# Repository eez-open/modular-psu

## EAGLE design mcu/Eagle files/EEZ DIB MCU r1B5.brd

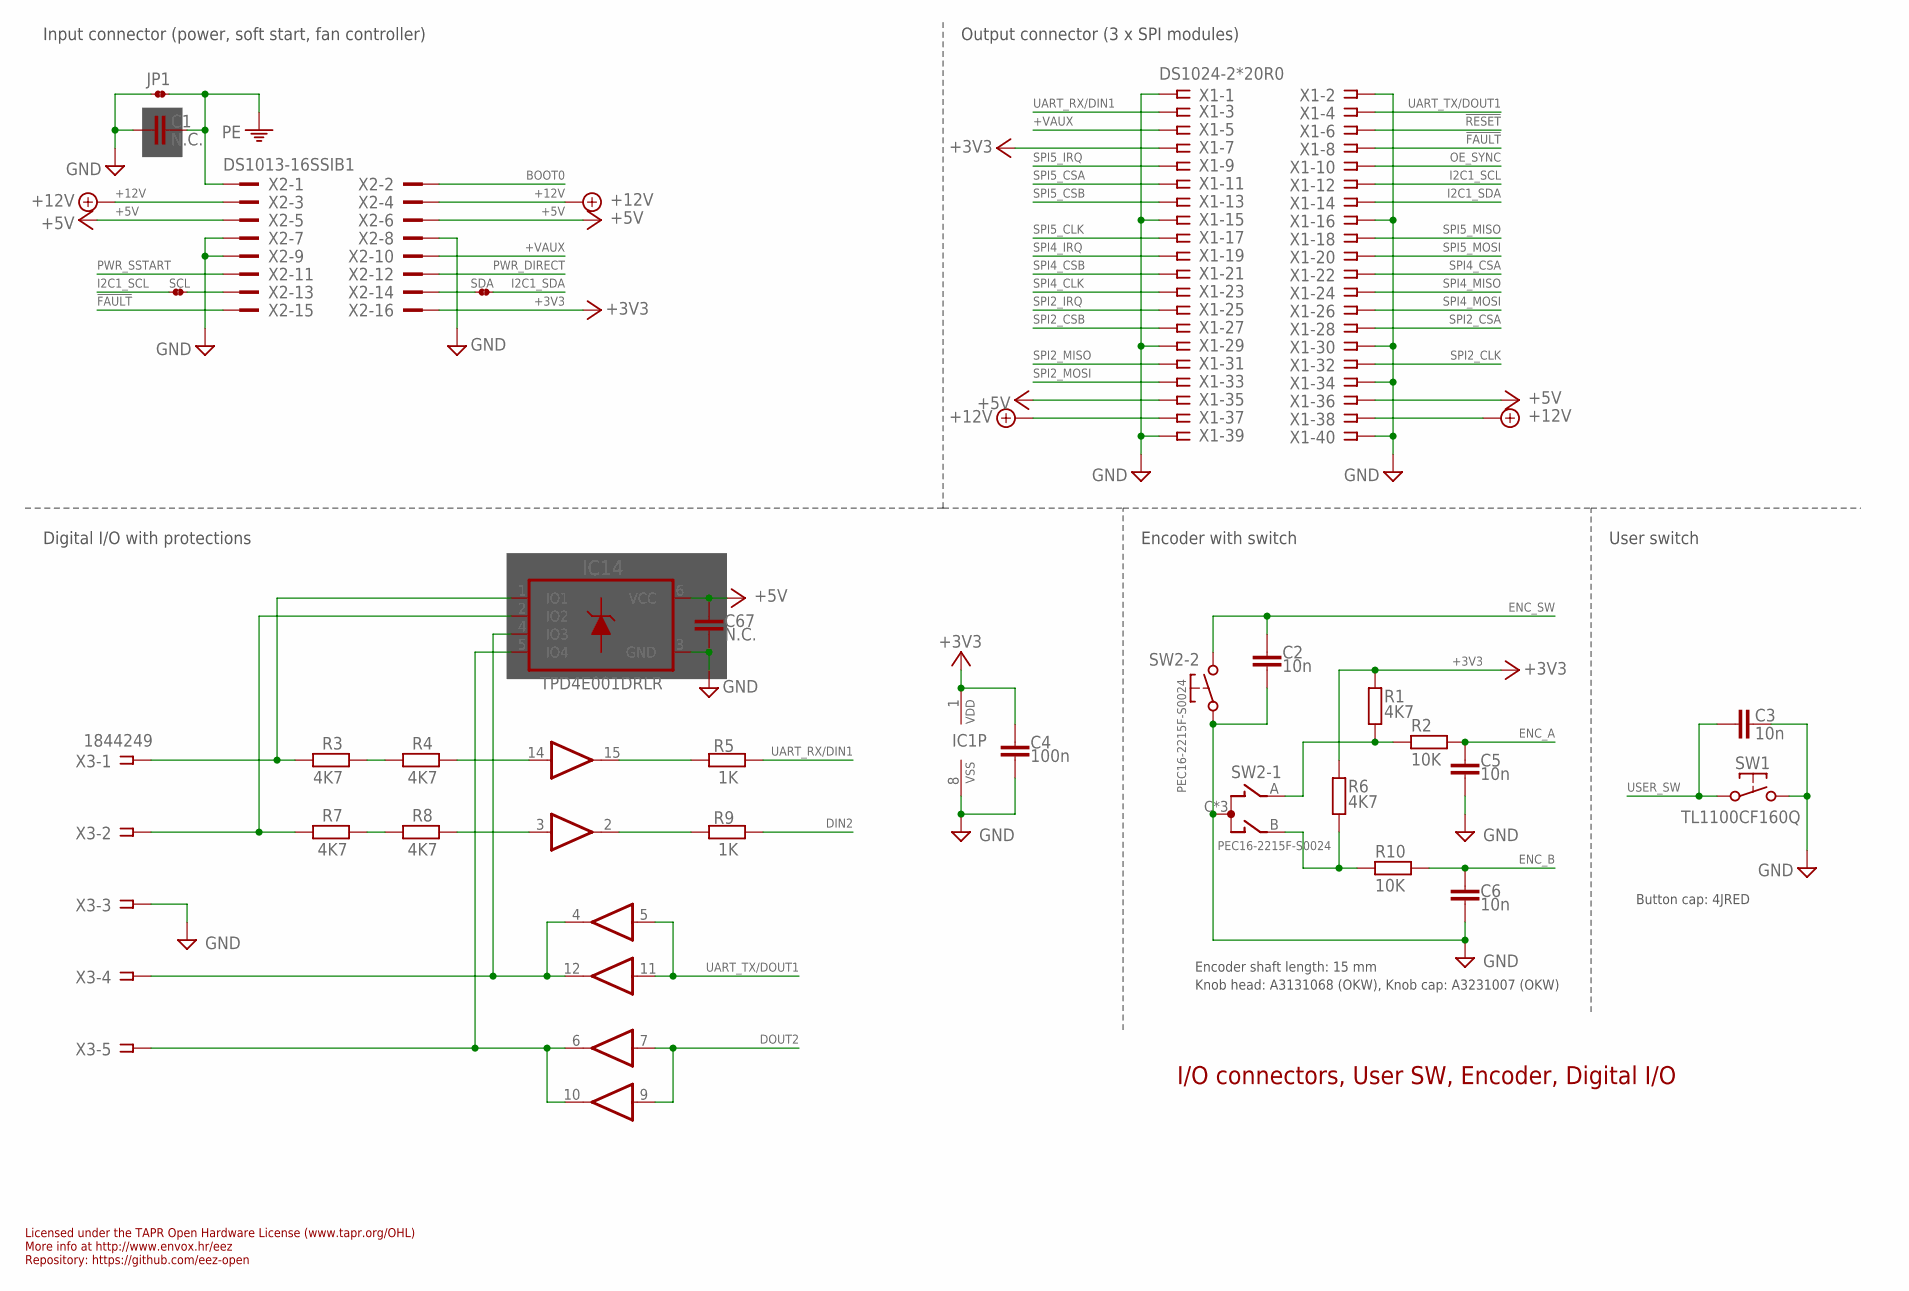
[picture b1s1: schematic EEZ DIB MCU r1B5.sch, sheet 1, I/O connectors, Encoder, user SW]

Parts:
C1: N.C.; C0805
C2, C3, C5, C6: 10n; C0805
C4: 100n; C0603
C67: N.C.; C0603
IC1: CD74HC4050PWR; PW16
IC14: TPD4E001DRLR; DRL6
JP1: JP2-NOCUT
R1, R3, R4, R6, R7, R8: 4K7; R0805
R2, R10: 10K; R0805
R5, R9: 1K; R0805
SCL: JP2-NOCUT
SDA: JP2-NOCUT
SW1: TL1100CF160Q; TL1100C
SW2: PEC16-2215F-S0024; PEC16-2215F
X1: DS1024-2*20R0; ZL263-40DG
X2: DS1013-16SSIB1; IDC-16PIN
X3: 1844249; MC1,5/5-G-3,5

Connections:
!FAULT: X1.8, X2.15; also elsewhere on the board
!RESET: X1.6; also elsewhere on the board
+3V3: C4.1, IC1.1 (VDD), R1.1, R6.1, X1.7, X2.16; also elsewhere on the board
+5V: C67.1, IC14.6 (VCC), X1.35, X1.36, X2.5, X2.6; also elsewhere on the board
+12V: X1.37, X1.38, X2.3, X2.4
+VAUX: X1.5, X2.10; also elsewhere on the board
BOOT0: X2.2; also elsewhere on the board
DIN2: R9.2; also elsewhere on the board
DOUT2: IC1.7 (I), IC1.9 (I); also elsewhere on the board
ENC_A: C5.2, R2.1; also elsewhere on the board
ENC_B: C6.1, R10.1; also elsewhere on the board
ENC_SW: C2.2, SW2.E (2); also elsewhere on the board
EOUT_A: R6.2, R10.2, SW2.B
EOUT_B: R1.2, R2.2, SW2.A
GND: C1.2, C2.1, C3.1, C4.2, C5.1, C6.2, C67.2, IC1.8 (VSS), IC14.3 (GND), JP1.1, SW1.2, SW2.C, SW2.D (1), SW2.GND1 (C), SW2.GND2 (C), X1.1, X1.2, X1.15, X1.16, X1.29, X1.30, X1.34, X1.39, X1.40, X2.7, X2.8, X2.9, X3.3; also elsewhere on the board
I2C1_SCL: SCL.1, X1.12; also elsewhere on the board
I2C1_SDA: SDA.2, X1.14; also elsewhere on the board
unnamed: IC14.1 (IO1), R3.1, X3.1
unnamed: SCL.2, X2.13
unnamed: SDA.1, X2.14
unnamed: IC14.2 (IO2), R7.1, X3.2
unnamed: R7.2, R8.1
unnamed: R3.2, R4.1
unnamed: IC1.15 (O), R5.1
unnamed: IC1.2 (O), R9.1
unnamed: IC1.14 (I), R4.2
unnamed: IC1.3 (I), R8.2
unnamed: IC1.4 (O), IC1.12 (O), IC14.4 (IO3), X3.4
unnamed: IC1.6 (O), IC1.10 (O), IC14.5 (IO4), X3.5
OE_SYNC: X1.10; also elsewhere on the board
PE: C1.1, JP1.2, X2.1; also elsewhere on the board
PWR_DIRECT: X2.12; also elsewhere on the board
PWR_SSTART: X2.11; also elsewhere on the board
SPI2_CLK: X1.32; also elsewhere on the board
SPI2_CSA: X1.28; also elsewhere on the board
SPI2_CSB: X1.27; also elsewhere on the board
SPI2_IRQ: X1.25; also elsewhere on the board
SPI2_MISO: X1.31; also elsewhere on the board
SPI2_MOSI: X1.33; also elsewhere on the board
SPI4_CLK: X1.23; also elsewhere on the board
SPI4_CSA: X1.22; also elsewhere on the board
SPI4_CSB: X1.21; also elsewhere on the board
SPI4_IRQ: X1.19; also elsewhere on the board
SPI4_MISO: X1.24; also elsewhere on the board
SPI4_MOSI: X1.26; also elsewhere on the board
SPI5_CLK: X1.17; also elsewhere on the board
SPI5_CSA: X1.11; also elsewhere on the board
SPI5_CSB: X1.13; also elsewhere on the board
SPI5_IRQ: X1.9; also elsewhere on the board
SPI5_MISO: X1.18; also elsewhere on the board
SPI5_MOSI: X1.20; also elsewhere on the board
UART_RX/DIN1: R5.2, X1.3; also elsewhere on the board
UART_TX/DOUT1: IC1.5 (I), IC1.11 (I), X1.4; also elsewhere on the board
USER_SW: C3.2, SW1.1; also elsewhere on the board

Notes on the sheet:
Licensed under the TAPR Open Hardware License (www.tapr.org/OHL)
Repository: https://github.com/eez-open
More info at http://www.envox.hr/eez
Encoder shaft length: 15 mm
Knob head: A3131068 (OKW), Knob cap: A3231007 (OKW)
I/O connectors, User SW, Encoder, Digital I/O
Digital I/O with protections
Encoder with switch
User switch
Input connector (power, soft start, fan controller)
Output connector (3 x SPI modules)
Button cap: 4JRED

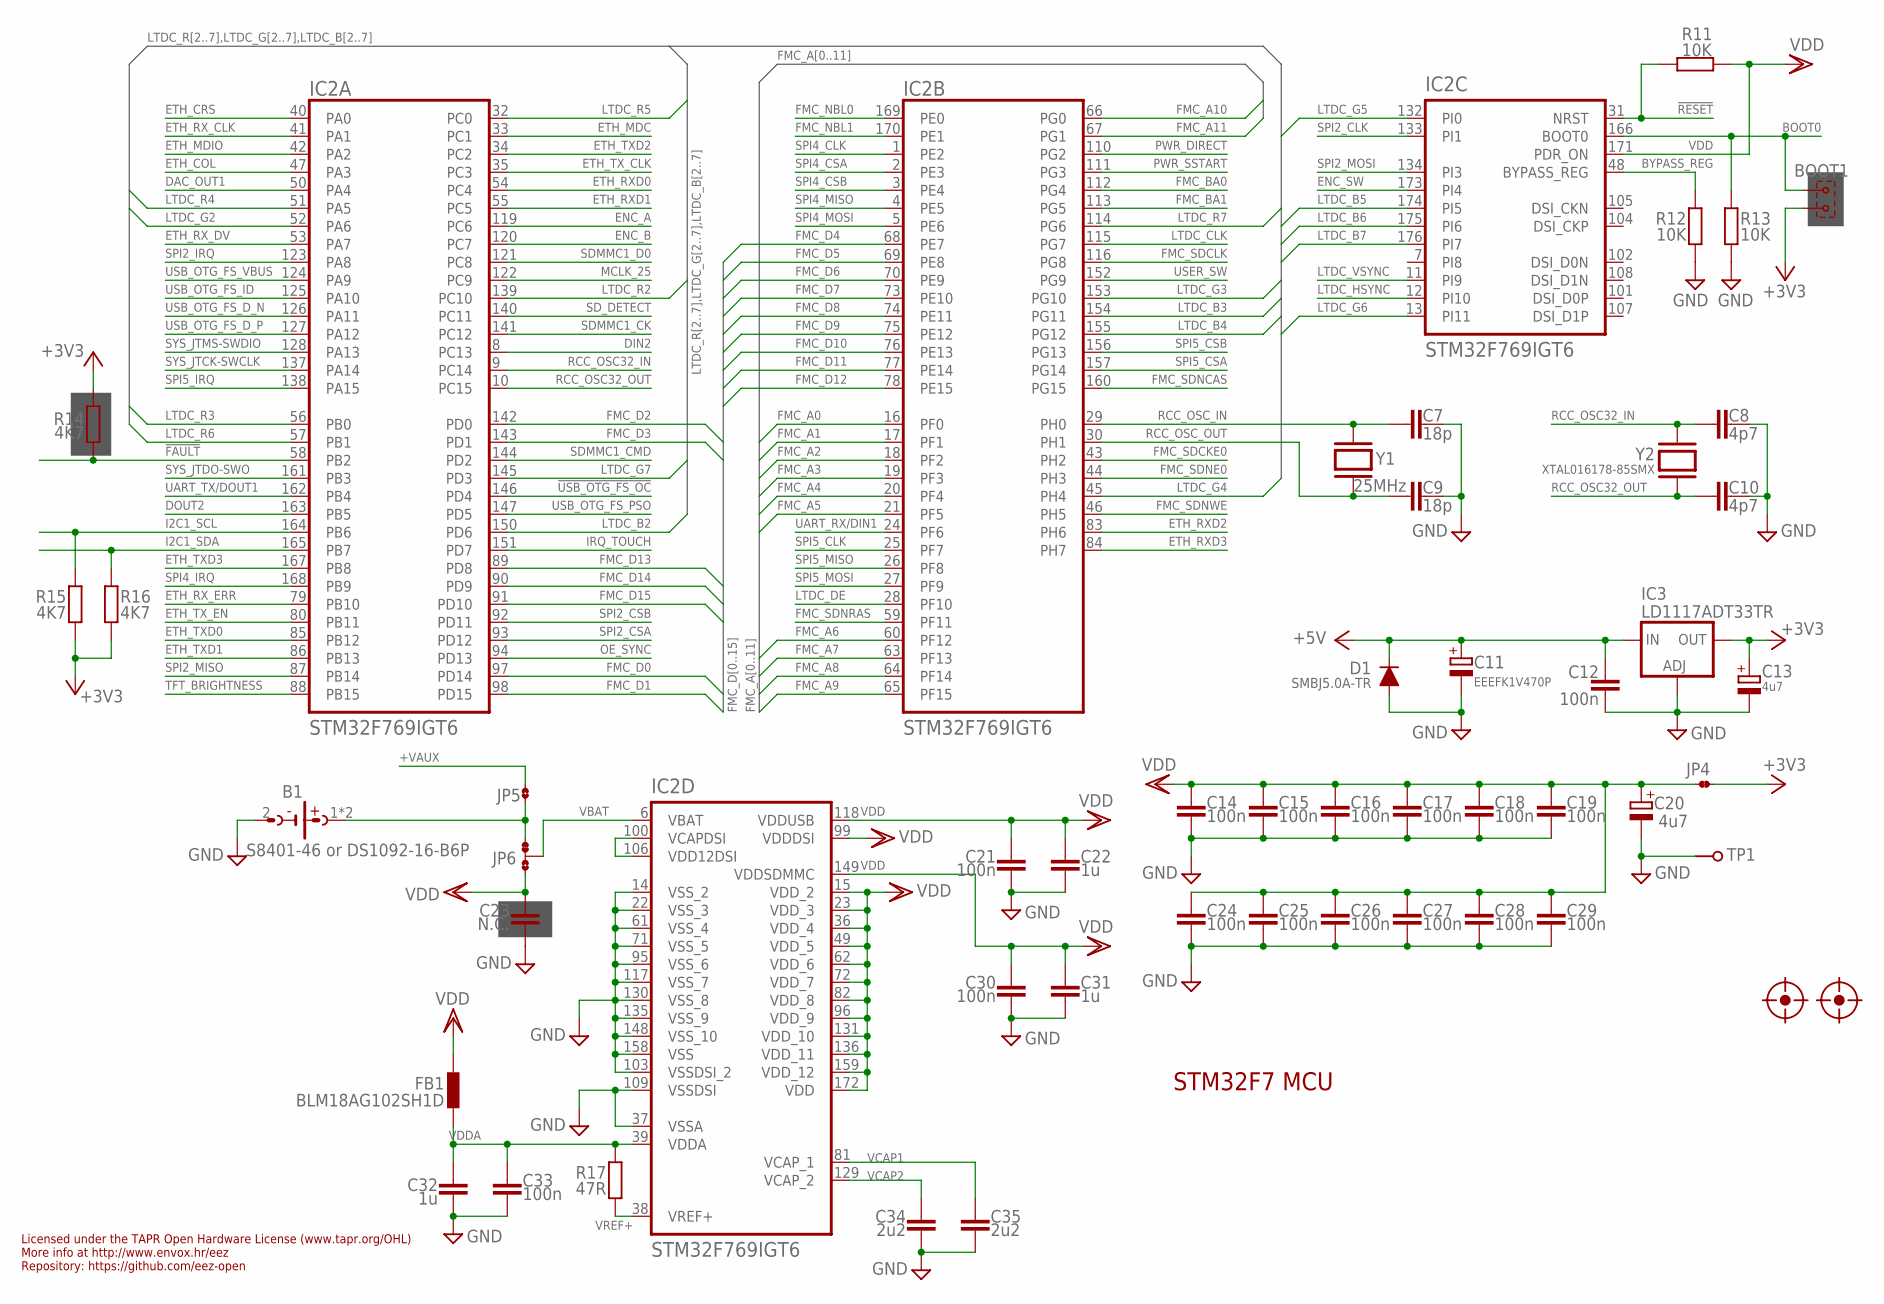
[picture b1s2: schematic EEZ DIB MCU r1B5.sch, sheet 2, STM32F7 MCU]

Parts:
B1: S8401-46 or DS1092-16-B6P; S8401-46
BOOT1: JUMPER-2PIN-2MM; 2MM-2
C7, C9: 18p; C0603
C8, C10: 4p7; C0603
C11: EEEFK1V470P; CAPAE660X610N
C12, C14, C15, C16, C17, C18, C19, C21, C24, C25, C26, C27, C28, C29, C30, C33: 100n; C0603
C13, C20: 4u7; EC1206
C22, C31, C32: 1u; C0805
C23: N.C.; C0603
C34, C35: 2u2; C0805
D1: SMBJ5.0A-TR; DO214AA
FB1: BLM18AG102SH1D; BEAD0603
FM1, FM2: FIDUCIAL
IC2: STM32F769IGT6; LQFP-176_24X24MM
IC3: LD1117ADT33TR; DPACK
JP4: JP2-NOCUT
JP5: JP2-CUT
JP6: JP3-CUT
R11, R12, R13: 10K; R0805
R14, R15, R16: 4K7; R0805
R17: 47R; R0805
TP1: PCB_TEST_TABSHIELD; PCB_SHIELD_TAB
Y1: 25MHz; HC-49/4H
Y2: XTAL016178-85SMX; 85SMX

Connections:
!FAULT: IC2.58 (PB2), R14.2; also elsewhere on the board
!RESET: IC2.31 (NRST), R11.2; also elsewhere on the board
!USB_OTG_FS_OC: IC2.146 (PD4); also elsewhere on the board
+3V3: BOOT1.2, C13.+, IC3.4 (OUT), JP4.2, R14.1, R15.1, R16.1; also elsewhere on the board
+5V: C11.1 (+), C12.1, D1.C, IC3.3 (IN); also elsewhere on the board
+VAUX: JP5.2; also elsewhere on the board
BOOT0: BOOT1.1, IC2.166 (BOOT0), R13.2; also elsewhere on the board
BYPASS_REG: IC2.48 (BYPASS_REG), R12.2
DAC_OUT1: IC2.50 (PA4); also elsewhere on the board
DIN2: IC2.8 (PC13); also elsewhere on the board
DOUT2: IC2.163 (PB5); also elsewhere on the board
ENC_A: IC2.119 (PC6); also elsewhere on the board
ENC_B: IC2.120 (PC7); also elsewhere on the board
ENC_SW: IC2.173 (PI4); also elsewhere on the board
ETH_COL: IC2.47 (PA3); also elsewhere on the board
ETH_CRS: IC2.40 (PA0); also elsewhere on the board
ETH_MDC: IC2.33 (PC1); also elsewhere on the board
ETH_MDIO: IC2.42 (PA2); also elsewhere on the board
ETH_RXD0: IC2.54 (PC4); also elsewhere on the board
ETH_RXD1: IC2.55 (PC5); also elsewhere on the board
ETH_RXD2: IC2.83 (PH6); also elsewhere on the board
ETH_RXD3: IC2.84 (PH7); also elsewhere on the board
ETH_RX_CLK: IC2.41 (PA1); also elsewhere on the board
ETH_RX_DV: IC2.53 (PA7); also elsewhere on the board
ETH_RX_ERR: IC2.79 (PB10); also elsewhere on the board
ETH_TXD0: IC2.85 (PB12); also elsewhere on the board
ETH_TXD1: IC2.86 (PB13); also elsewhere on the board
ETH_TXD2: IC2.34 (PC2); also elsewhere on the board
ETH_TXD3: IC2.167 (PB8); also elsewhere on the board
ETH_TX_CLK: IC2.35 (PC3); also elsewhere on the board
ETH_TX_EN: IC2.80 (PB11); also elsewhere on the board
FMC_A0: IC2.16 (PF0); also elsewhere on the board
FMC_A1: IC2.17 (PF1); also elsewhere on the board
FMC_A2: IC2.18 (PF2); also elsewhere on the board
FMC_A3: IC2.19 (PF3); also elsewhere on the board
FMC_A4: IC2.20 (PF4); also elsewhere on the board
FMC_A5: IC2.21 (PF5); also elsewhere on the board
FMC_A6: IC2.60 (PF12); also elsewhere on the board
FMC_A7: IC2.63 (PF13); also elsewhere on the board
FMC_A8: IC2.64 (PF14); also elsewhere on the board
FMC_A9: IC2.65 (PF15); also elsewhere on the board
FMC_A10: IC2.66 (PG0); also elsewhere on the board
FMC_A11: IC2.67 (PG1); also elsewhere on the board
FMC_BA0: IC2.112 (PG4); also elsewhere on the board
FMC_BA1: IC2.113 (PG5); also elsewhere on the board
FMC_D0: IC2.97 (PD14); also elsewhere on the board
FMC_D1: IC2.98 (PD15); also elsewhere on the board
FMC_D2: IC2.142 (PD0); also elsewhere on the board
FMC_D3: IC2.143 (PD1); also elsewhere on the board
FMC_D4: IC2.68 (PE7); also elsewhere on the board
FMC_D5: IC2.69 (PE8); also elsewhere on the board
FMC_D6: IC2.70 (PE9); also elsewhere on the board
FMC_D7: IC2.73 (PE10); also elsewhere on the board
FMC_D8: IC2.74 (PE11); also elsewhere on the board
FMC_D9: IC2.75 (PE12); also elsewhere on the board
FMC_D10: IC2.76 (PE13); also elsewhere on the board
FMC_D11: IC2.77 (PE14); also elsewhere on the board
FMC_D12: IC2.78 (PE15); also elsewhere on the board
FMC_D13: IC2.89 (PD8); also elsewhere on the board
FMC_D14: IC2.90 (PD9); also elsewhere on the board
FMC_D15: IC2.91 (PD10); also elsewhere on the board
FMC_NBL0: IC2.169 (PE0); also elsewhere on the board
FMC_NBL1: IC2.170 (PE1); also elsewhere on the board
FMC_SDCKE0: IC2.43 (PH2); also elsewhere on the board
FMC_SDCLK: IC2.116 (PG8); also elsewhere on the board
FMC_SDNCAS: IC2.160 (PG15); also elsewhere on the board
FMC_SDNE0: IC2.44 (PH3); also elsewhere on the board
FMC_SDNRAS: IC2.59 (PF11); also elsewhere on the board
FMC_SDNWE: IC2.46 (PH5); also elsewhere on the board
GND: B1.2 (-), C7.1, C8.2, C9.1, C10.2, C11.2 (-), C12.2, C13.-, C14.2, C15.2, C16.2, C17.2, C18.2, C19.2, C20.-, C21.2, C22.2, C23.2, C24.2, C25.2, C26.2, C27.2, C28.2, C29.2, C30.2, C31.2, C32.2, C33.2, C34.2, C35.2, D1.A, IC2.14 (VSS_2), IC2.22 (VSS_3), IC2.37 (VSSA), IC2.61 (VSS_4), IC2.71 (VSS_5), IC2.95 (VSS_6), IC2.103 (VSSDSI_2), IC2.109 (VSSDSI), IC2.117 (VSS_7), IC2.130 (VSS_8), IC2.135 (VSS_9), IC2.148 (VSS_10), IC2.158 (VSS), IC3.1 (ADJ), R12.1, R13.1, TP1.1; also elsewhere on the board
I2C1_SCL: IC2.164 (PB6), R15.2; also elsewhere on the board
I2C1_SDA: IC2.165 (PB7), R16.2; also elsewhere on the board
IRQ_TOUCH: IC2.151 (PD7); also elsewhere on the board
LTDC_B2: IC2.150 (PD6); also elsewhere on the board
LTDC_B3: IC2.154 (PG11); also elsewhere on the board
LTDC_B4: IC2.155 (PG12); also elsewhere on the board
LTDC_B5: IC2.174 (PI5); also elsewhere on the board
LTDC_B6: IC2.175 (PI6); also elsewhere on the board
LTDC_B7: IC2.176 (PI7); also elsewhere on the board
LTDC_CLK: IC2.115 (PG7); also elsewhere on the board
LTDC_DE: IC2.28 (PF10); also elsewhere on the board
LTDC_G2: IC2.52 (PA6); also elsewhere on the board
LTDC_G3: IC2.153 (PG10); also elsewhere on the board
LTDC_G4: IC2.45 (PH4); also elsewhere on the board
LTDC_G5: IC2.132 (PI0); also elsewhere on the board
LTDC_G6: IC2.13 (PI11); also elsewhere on the board
LTDC_G7: IC2.145 (PD3); also elsewhere on the board
LTDC_HSYNC: IC2.12 (PI10); also elsewhere on the board
LTDC_R2: IC2.139 (PC10); also elsewhere on the board
LTDC_R3: IC2.56 (PB0); also elsewhere on the board
LTDC_R4: IC2.51 (PA5); also elsewhere on the board
LTDC_R5: IC2.32 (PC0); also elsewhere on the board
LTDC_R6: IC2.57 (PB1); also elsewhere on the board
LTDC_R7: IC2.114 (PG6); also elsewhere on the board
LTDC_VSYNC: IC2.11 (PI9); also elsewhere on the board
MCLK_25: IC2.122 (PC9); also elsewhere on the board
unnamed: B1.1 (+), B1.3 (+), JP5.1, JP6.NC
unnamed: IC2.100 (VCAPDSI), IC2.106 (VDD12DSI)
OE_SYNC: IC2.94 (PD13); also elsewhere on the board
PWR_DIRECT: IC2.110 (PG2); also elsewhere on the board
PWR_SSTART: IC2.111 (PG3); also elsewhere on the board
RCC_OSC32_IN: C8.1, IC2.9 (PC14), Y2.1
RCC_OSC32_OUT: C10.1, IC2.10 (PC15), Y2.4 (2)
RCC_OSC_IN: C7.2, IC2.29 (PH0), Y1.2
RCC_OSC_OUT: C9.2, IC2.30 (PH1), Y1.1
SDMMC1_CK: IC2.141 (PC12); also elsewhere on the board
SDMMC1_CMD: IC2.144 (PD2); also elsewhere on the board
SDMMC1_D0: IC2.121 (PC8); also elsewhere on the board
SD_DETECT: IC2.140 (PC11); also elsewhere on the board
SPI2_CLK: IC2.133 (PI1); also elsewhere on the board
SPI2_CSA: IC2.93 (PD12); also elsewhere on the board
SPI2_CSB: IC2.92 (PD11); also elsewhere on the board
SPI2_IRQ: IC2.123 (PA8); also elsewhere on the board
SPI2_MISO: IC2.87 (PB14); also elsewhere on the board
SPI2_MOSI: IC2.134 (PI3); also elsewhere on the board
SPI4_CLK: IC2.1 (PE2); also elsewhere on the board
SPI4_CSA: IC2.2 (PE3); also elsewhere on the board
SPI4_CSB: IC2.3 (PE4); also elsewhere on the board
SPI4_IRQ: IC2.168 (PB9); also elsewhere on the board
SPI4_MISO: IC2.4 (PE5); also elsewhere on the board
SPI4_MOSI: IC2.5 (PE6); also elsewhere on the board
SPI5_CLK: IC2.25 (PF7); also elsewhere on the board
SPI5_CSA: IC2.157 (PG14); also elsewhere on the board
SPI5_CSB: IC2.156 (PG13); also elsewhere on the board
SPI5_IRQ: IC2.138 (PA15); also elsewhere on the board
SPI5_MISO: IC2.26 (PF8); also elsewhere on the board
SPI5_MOSI: IC2.27 (PF9); also elsewhere on the board
SYS_JTCK-SWCLK: IC2.137 (PA14); also elsewhere on the board
SYS_JTDO-SWO: IC2.161 (PB3); also elsewhere on the board
SYS_JTMS-SWDIO: IC2.128 (PA13); also elsewhere on the board
TFT_BRIGHTNESS: IC2.88 (PB15); also elsewhere on the board
UART_RX/DIN1: IC2.24 (PF6); also elsewhere on the board
UART_TX/DOUT1: IC2.162 (PB4); also elsewhere on the board
USB_OTG_FS_D_N: IC2.126 (PA11); also elsewhere on the board
USB_OTG_FS_D_P: IC2.127 (PA12); also elsewhere on the board
USB_OTG_FS_ID: IC2.125 (PA10); also elsewhere on the board
USB_OTG_FS_PSO: IC2.147 (PD5); also elsewhere on the board
USB_OTG_FS_VBUS: IC2.124 (PA9); also elsewhere on the board
USER_SW: IC2.152 (PG9); also elsewhere on the board
VBAT: IC2.6 (VBAT), JP6.COM
VCAP1: C35.1, IC2.81 (VCAP_1)
VCAP2: C34.1, IC2.129 (VCAP_2)
VDD: C14.1, C15.1, C16.1, C17.1, C18.1, C19.1, C20.+, C21.1, C22.1, C23.1, C24.1, C25.1, C26.1, C27.1, C28.1, C29.1, C30.1, C31.1, FB1.P$1 (1), IC2.15 (VDD_2), IC2.23 (VDD_3), IC2.36 (VDD_4), IC2.49 (VDD_5), IC2.62 (VDD_6), IC2.72 (VDD_7), IC2.82 (VDD_8), IC2.96 (VDD_9), IC2.99 (VDDDSI), IC2.118 (VDDUSB), IC2.131 (VDD_10), IC2.136 (VDD_11), IC2.149 (VDDSDMMC), IC2.159 (VDD_12), IC2.171 (PDR_ON), IC2.172 (VDD), JP4.1, JP6.NO, R11.1
VDDA: C32.1, C33.1, FB1.P$2 (2), IC2.39 (VDDA), R17.2
VREF+: IC2.38 (VREF+), R17.1

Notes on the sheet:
Licensed under the TAPR Open Hardware License (www.tapr.org/OHL)
Repository: https://github.com/eez-open
More info at http://www.envox.hr/eez
STM32F7 MCU

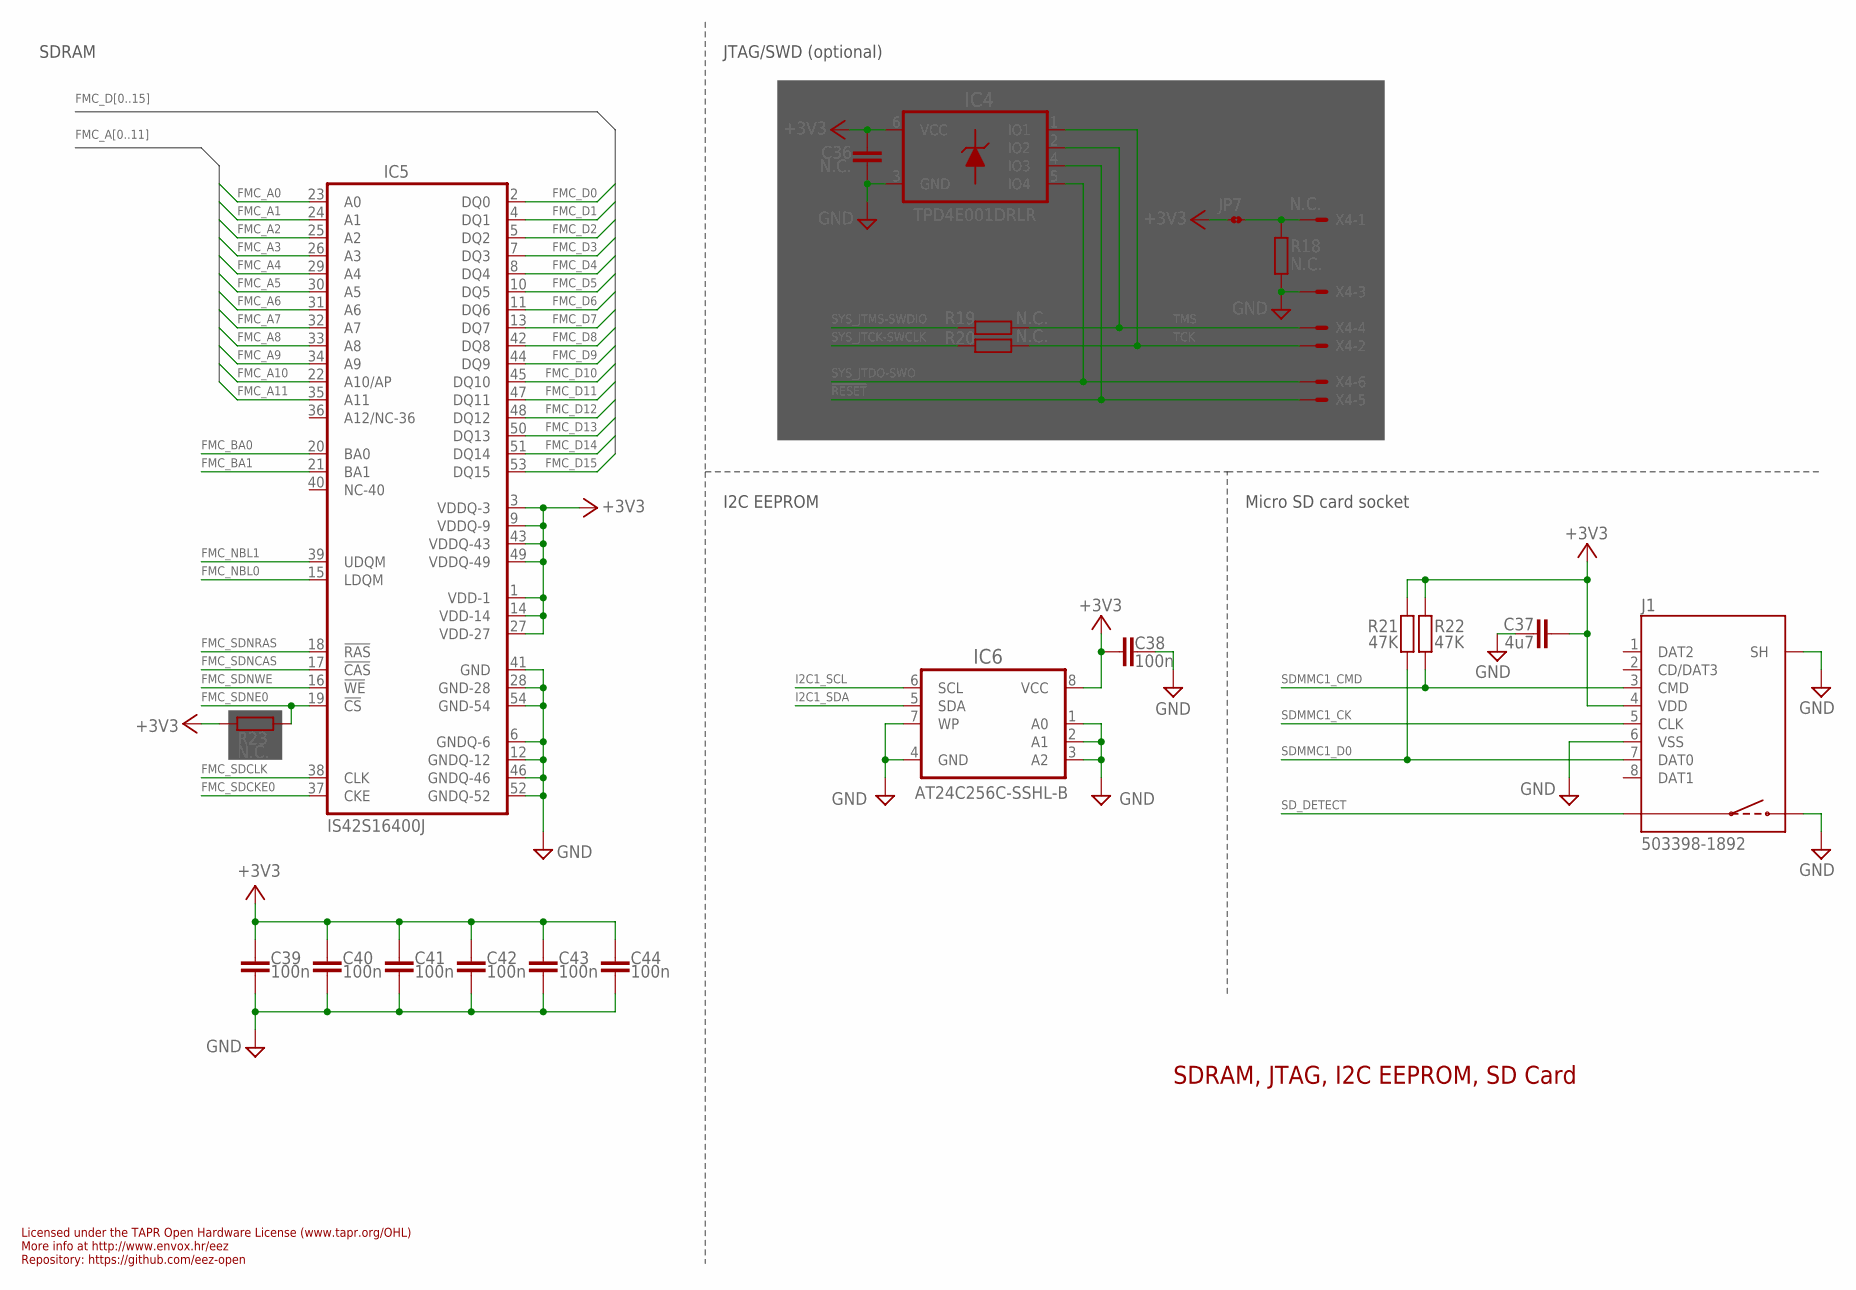
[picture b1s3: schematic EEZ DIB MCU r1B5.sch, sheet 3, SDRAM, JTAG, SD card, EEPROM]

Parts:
C36: N.C.; C0603
C37: 4u7; C1206
C38, C39, C40, C41, C42, C43, C44: 100n; C0603
IC4: TPD4E001DRLR; DRL6
IC5: IS42S16400J; TSOPII-54
IC6: AT24C256C-SSHL-B; SOIC127P600X173-8N
J1: 503398-1892; 5033981892
JP7: JP2-CUT
R18, R19, R20, R23: N.C.; R0805
R21, R22: 47K; R0805
X4: N.C.; 22-23-2061

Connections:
!RESET: IC4.4 (IO3), X4.5; also elsewhere on the board
+3V3: C36.1, C37.1, C38.2, C39.1, C40.1, C41.1, C42.1, C43.1, C44.1, IC4.6 (VCC), IC5.1 (VDD-1), IC5.3 (VDDQ-3), IC5.9 (VDDQ-9), IC5.14 (VDD-14), IC5.27 (VDD-27), IC5.43 (VDDQ-43), IC5.49 (VDDQ-49), IC6.8 (VCC), J1.4 (VDD), JP7.1, R21.1, R22.1, R23.1; also elsewhere on the board
FMC_A0: IC5.23 (A0); also elsewhere on the board
FMC_A1: IC5.24 (A1); also elsewhere on the board
FMC_A2: IC5.25 (A2); also elsewhere on the board
FMC_A3: IC5.26 (A3); also elsewhere on the board
FMC_A4: IC5.29 (A4); also elsewhere on the board
FMC_A5: IC5.30 (A5); also elsewhere on the board
FMC_A6: IC5.31 (A6); also elsewhere on the board
FMC_A7: IC5.32 (A7); also elsewhere on the board
FMC_A8: IC5.33 (A8); also elsewhere on the board
FMC_A9: IC5.34 (A9); also elsewhere on the board
FMC_A10: IC5.22 (A10/AP); also elsewhere on the board
FMC_A11: IC5.35 (A11); also elsewhere on the board
FMC_BA0: IC5.20 (BA0); also elsewhere on the board
FMC_BA1: IC5.21 (BA1); also elsewhere on the board
FMC_D0: IC5.2 (DQ0); also elsewhere on the board
FMC_D1: IC5.4 (DQ1); also elsewhere on the board
FMC_D2: IC5.5 (DQ2); also elsewhere on the board
FMC_D3: IC5.7 (DQ3); also elsewhere on the board
FMC_D4: IC5.8 (DQ4); also elsewhere on the board
FMC_D5: IC5.10 (DQ5); also elsewhere on the board
FMC_D6: IC5.11 (DQ6); also elsewhere on the board
FMC_D7: IC5.13 (DQ7); also elsewhere on the board
FMC_D8: IC5.42 (DQ8); also elsewhere on the board
FMC_D9: IC5.44 (DQ9); also elsewhere on the board
FMC_D10: IC5.45 (DQ10); also elsewhere on the board
FMC_D11: IC5.47 (DQ11); also elsewhere on the board
FMC_D12: IC5.48 (DQ12); also elsewhere on the board
FMC_D13: IC5.50 (DQ13); also elsewhere on the board
FMC_D14: IC5.51 (DQ14); also elsewhere on the board
FMC_D15: IC5.53 (DQ15); also elsewhere on the board
FMC_NBL0: IC5.15 (LDQM); also elsewhere on the board
FMC_NBL1: IC5.39 (UDQM); also elsewhere on the board
FMC_SDCKE0: IC5.37 (CKE); also elsewhere on the board
FMC_SDCLK: IC5.38 (CLK); also elsewhere on the board
FMC_SDNCAS: IC5.17 (!CAS); also elsewhere on the board
FMC_SDNE0: IC5.19 (!CS), R23.2; also elsewhere on the board
FMC_SDNRAS: IC5.18 (!RAS); also elsewhere on the board
FMC_SDNWE: IC5.16 (!WE); also elsewhere on the board
GND: C36.2, C37.2, C38.1, C39.2, C40.2, C41.2, C42.2, C43.2, C44.2, IC4.3 (GND), IC5.6 (GNDQ-6), IC5.12 (GNDQ-12), IC5.28 (GND-28), IC5.41 (GND), IC5.46 (GNDQ-46), IC5.52 (GNDQ-52), IC5.54 (GND-54), IC6.1 (A0), IC6.2 (A1), IC6.3 (A2), IC6.4 (GND), IC6.7 (WP), J1.6 (VSS), J1.S (SH), J1.S1 (SH), J1.S2 (SH), J1.SW2, R18.1, X4.3; also elsewhere on the board
I2C1_SCL: IC6.6 (SCL); also elsewhere on the board
I2C1_SDA: IC6.5 (SDA); also elsewhere on the board
unnamed: JP7.2, R18.2, X4.1
SDMMC1_CK: J1.5 (CLK); also elsewhere on the board
SDMMC1_CMD: J1.3 (CMD), R22.2; also elsewhere on the board
SDMMC1_D0: J1.7 (DAT0), R21.2; also elsewhere on the board
SD_DETECT: J1.SW1; also elsewhere on the board
SYS_JTCK-SWCLK: R20.1; also elsewhere on the board
SYS_JTDO-SWO: IC4.5 (IO4), X4.6; also elsewhere on the board
SYS_JTMS-SWDIO: R19.1; also elsewhere on the board
TCK: IC4.1 (IO1), R20.2, X4.2
TMS: IC4.2 (IO2), R19.2, X4.4

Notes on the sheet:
SDRAM, JTAG, I2C EEPROM, SD Card
Licensed under the TAPR Open Hardware License (www.tapr.org/OHL)
Repository: https://github.com/eez-open
More info at http://www.envox.hr/eez
I2C EEPROM
Micro SD card socket
JTAG/SWD (optional)
SDRAM

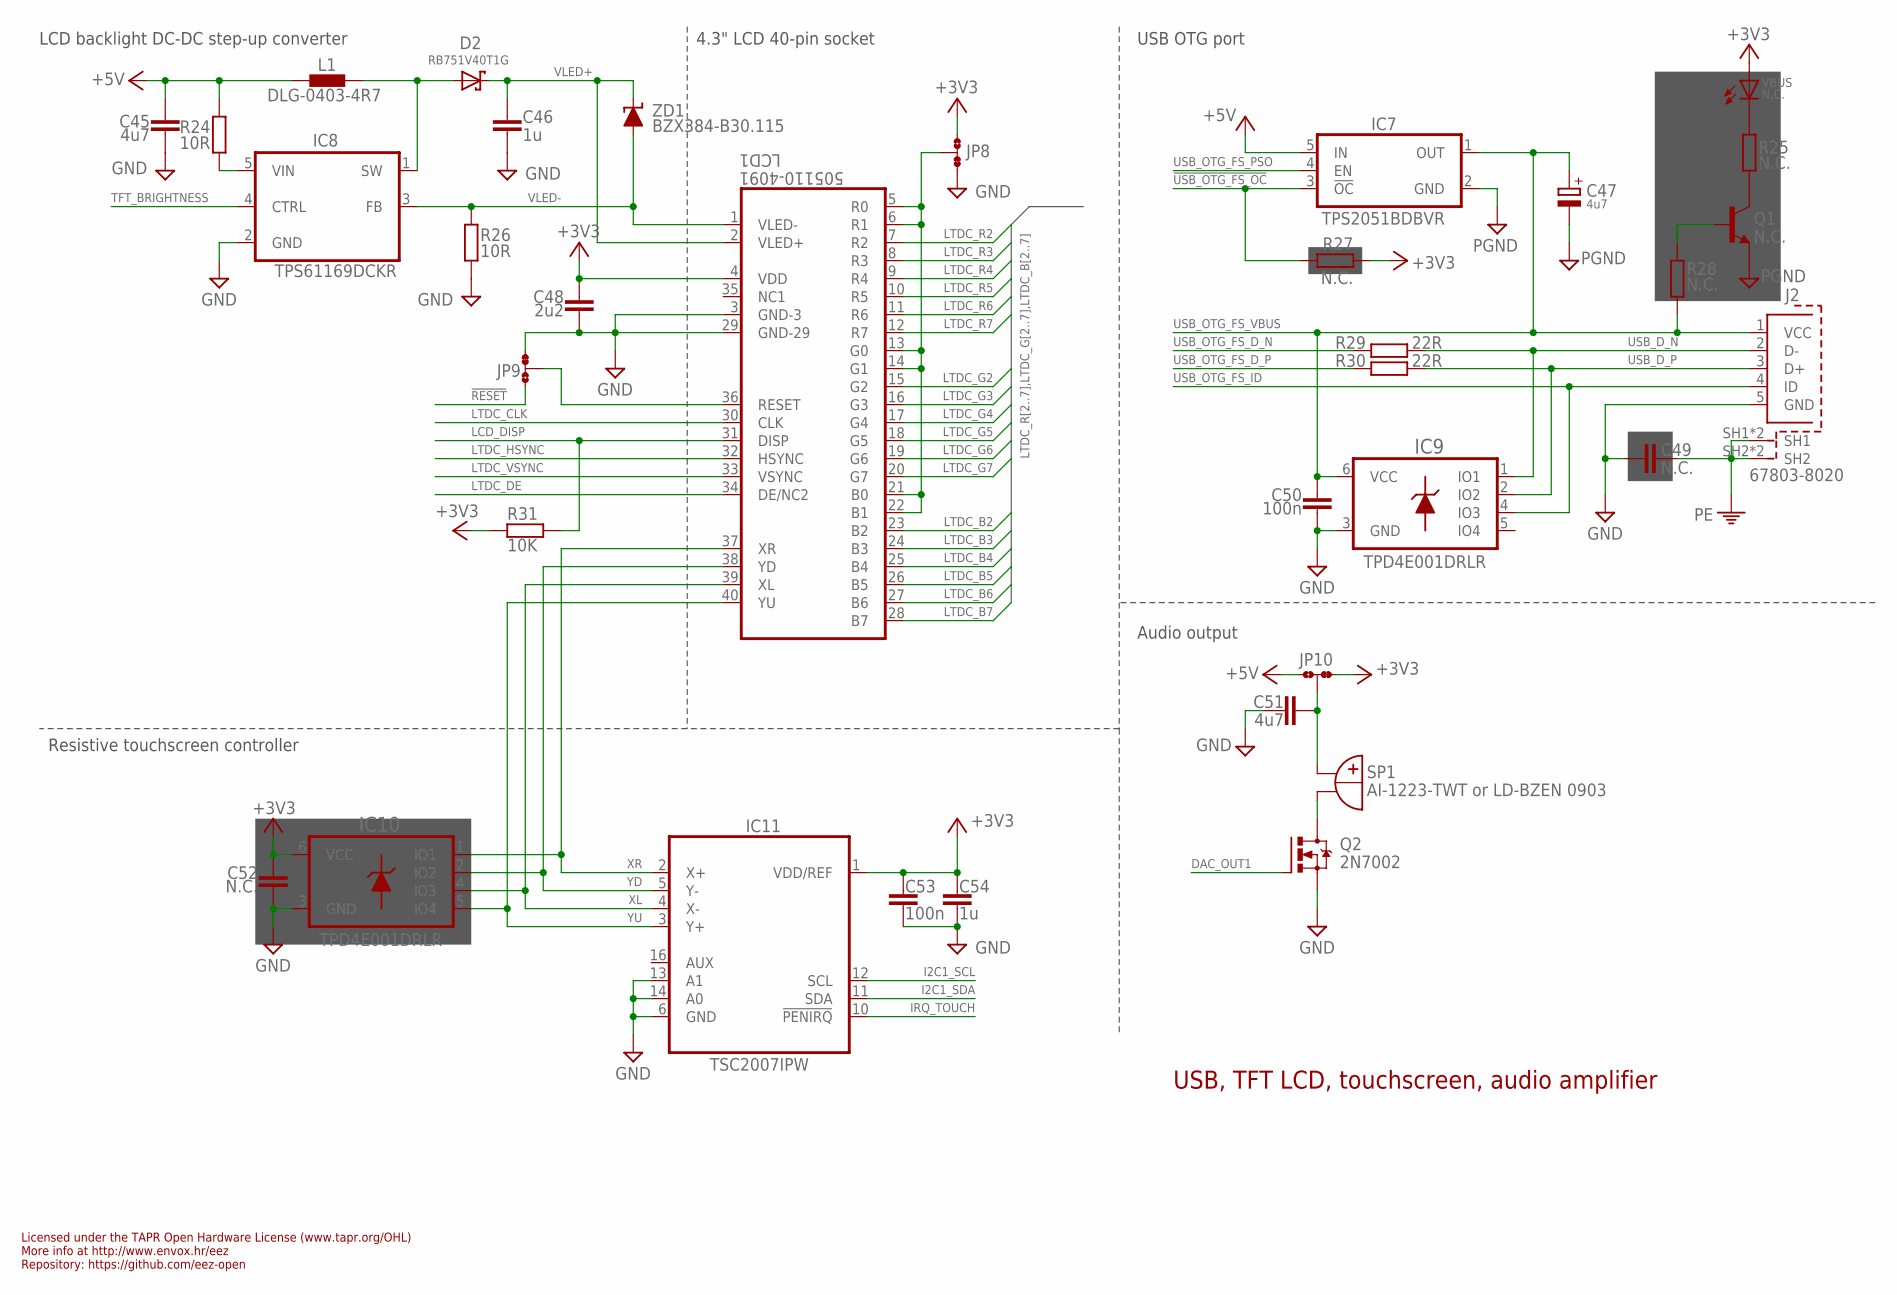
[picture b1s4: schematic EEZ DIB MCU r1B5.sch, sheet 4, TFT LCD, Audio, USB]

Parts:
C45, C51: 4u7; C1206
C46, C54: 1u; C0805
C47: 4u7; EC1206
C48: 2u2; C0805
C49: N.C.; C0805
C50, C53: 100n; C0603
C52: N.C.; C0603
D2: RB751V40T1G; SOD323-R
IC7: TPS2051BDBVR; DBV5
IC8: TPS61169DCKR; DCK5
IC9, IC10: TPD4E001DRLR; DRL6
IC11: TSC2007IPW; PW(R-PDSO-G16)
J2: 67803-8020; 678038020
JP8, JP9, JP10: JP3-CUT
L1: DLG-0403-4R7; DE0403
LCD1: 505110-4091; FPC_40
Q1: N.C.; SOT23-BEC
Q2: 2N7002; SOT103P240X110-3N
R24, R26: 10R; R0805
R25, R27, R28: N.C.; R0805
R29, R30: 22R; R0805
R31: 10K; R0805
SP1: AI-1223-TWT or LD-BZEN 0903; AI-1223-TWT_COMBO
VBUS: N.C.; LED_0805
ZD1: BZX384-B30.115; SOD323-W

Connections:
!RESET: JP9.NO; also elsewhere on the board
!USB_OTG_FS_OC: IC7.3 (!OC), R27.1; also elsewhere on the board
+3V3: C48.1, C52.2, C53.2, C54.2, IC10.6 (VCC), IC11.1 (VDD/REF), JP8.NO, JP10.NC, LCD1.4 (VDD), R27.2, R31.2, VBUS.A; also elsewhere on the board
+5V: C45.1, IC7.5 (IN), JP10.NO, L1.1, R24.1; also elsewhere on the board
DAC_OUT1: Q2.1 (G); also elsewhere on the board
GND: C45.2, C46.2, C47.-, C48.2, C49.2, C50.1, C51.1, C52.1, C53.1, C54.1, IC7.2 (GND), IC8.2 (GND), IC9.3 (GND), IC10.3 (GND), IC11.6 (GND), IC11.13 (A1), IC11.14 (A0), J2.5 (GND), JP8.NC, JP9.NC, LCD1.3 (GND-3), LCD1.29 (GND-29), Q1.E, Q2.2 (S), R26.2; also elsewhere on the board
I2C1_SCL: IC11.12 (SCL); also elsewhere on the board
I2C1_SDA: IC11.11 (SDA); also elsewhere on the board
IRQ_TOUCH: IC11.10 (!PENIRQ); also elsewhere on the board
LCD_DISP: LCD1.31 (DISP), R31.1
LTDC_B2: LCD1.23 (B2); also elsewhere on the board
LTDC_B3: LCD1.24 (B3); also elsewhere on the board
LTDC_B4: LCD1.25 (B4); also elsewhere on the board
LTDC_B5: LCD1.26 (B5); also elsewhere on the board
LTDC_B6: LCD1.27 (B6); also elsewhere on the board
LTDC_B7: LCD1.28 (B7); also elsewhere on the board
LTDC_CLK: LCD1.30 (CLK); also elsewhere on the board
LTDC_DE: LCD1.34 (DE/NC2); also elsewhere on the board
LTDC_G2: LCD1.15 (G2); also elsewhere on the board
LTDC_G3: LCD1.16 (G3); also elsewhere on the board
LTDC_G4: LCD1.17 (G4); also elsewhere on the board
LTDC_G5: LCD1.18 (G5); also elsewhere on the board
LTDC_G6: LCD1.19 (G6); also elsewhere on the board
LTDC_G7: LCD1.20 (G7); also elsewhere on the board
LTDC_HSYNC: LCD1.32 (HSYNC); also elsewhere on the board
LTDC_R2: LCD1.7 (R2); also elsewhere on the board
LTDC_R3: LCD1.8 (R3); also elsewhere on the board
LTDC_R4: LCD1.9 (R4); also elsewhere on the board
LTDC_R5: LCD1.10 (R5); also elsewhere on the board
LTDC_R6: LCD1.11 (R6); also elsewhere on the board
LTDC_R7: LCD1.12 (R7); also elsewhere on the board
LTDC_VSYNC: LCD1.33 (VSYNC); also elsewhere on the board
unnamed: R25.2, VBUS.C
unnamed: JP8.COM, LCD1.5 (R0), LCD1.6 (R1), LCD1.13 (G0), LCD1.14 (G1), LCD1.21 (B0), LCD1.22 (B1)
unnamed: Q2.3 (D), SP1.-B (-), SP1.-B.1 (-)
unnamed: Q1.C, R25.1
unnamed: Q1.B, R28.2
unnamed: JP9.COM, LCD1.36 (RESET)
unnamed: IC8.5 (VIN), R24.2
unnamed: C51.2, JP10.COM, SP1.+B (+), SP1.+B.1 (+)
PE: C49.1, J2.SH1, J2.SH1.1 (SH1), J2.SH2, J2.SH2.2 (SH2); also elsewhere on the board
SW_WLED: D2.A, IC8.1 (SW), L1.2
TFT_BRIGHTNESS: IC8.4 (CTRL); also elsewhere on the board
USB_D_N: IC9.1 (IO1), J2.2 (D-), R29.1
USB_D_P: IC9.2 (IO2), J2.3 (D+), R30.1
USB_OTG_FS_D_N: R29.2; also elsewhere on the board
USB_OTG_FS_D_P: R30.2; also elsewhere on the board
USB_OTG_FS_ID: IC9.4 (IO3), J2.4 (ID); also elsewhere on the board
USB_OTG_FS_PSO: IC7.4 (EN); also elsewhere on the board
USB_OTG_FS_VBUS: C47.+, C50.2, IC7.1 (OUT), IC9.6 (VCC), J2.1 (VCC), R28.1; also elsewhere on the board
VLED+: C46.1, D2.C, LCD1.2 (VLED+), ZD1.C
VLED-: IC8.3 (FB), LCD1.1 (VLED-), R26.1, ZD1.A
XL: IC10.4 (IO3), IC11.4 (X-), LCD1.39 (XL)
XR: IC10.1 (IO1), IC11.2 (X+), LCD1.37 (XR)
YD: IC10.2 (IO2), IC11.5 (Y-), LCD1.38 (YD)
YU: IC10.5 (IO4), IC11.3 (Y+), LCD1.40 (YU)

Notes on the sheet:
USB, TFT LCD, touchscreen, audio amplifier
Licensed under the TAPR Open Hardware License (www.tapr.org/OHL)
Repository: https://github.com/eez-open
More info at http://www.envox.hr/eez
4.3" LCD 40-pin socket
LCD backlight DC-DC step-up converter
USB OTG port
Resistive touchscreen controller
Audio output

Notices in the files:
parts and their libraries:
EEZ_DIB: This work is licensed under the TAPR Open Hardware License.
COPYRIGHT: Copyright C 2016 Accelerated Designs. All rights reserved
